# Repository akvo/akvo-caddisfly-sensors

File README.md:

This repository contain source files for fabricating the environmental sensors developed by Akvo in partnership with SODAQ and REGGS. The files are stored in two folders:

*hardware-packaging*: contains design files for the plastic and aluminum components, as well as photography, stickers, and packaging.

The abbreviations stand for:

* WEC: Water EC sensor
* SEC: Soil EC sensor
* SOM: Soil Moisture sensor
* SUM: Stove Usage Monitoring sensor
* WAP: Water pressure sensor
* HAP: House Air Pollution sensor
* SSU: Standard Surface Unit

*pcb-software-manuals*: contains design files for the PCB's, including manuals, firmware and supporting software.

Each device folder includes:

Hardware files : Eagle CAD files for the schematic and gerbers, including a bill of materials (BOM).

Software files : arduino files and associated libraries

Manual : in pdf & markdown format

License
Copyright (C) Stichting Akvo (Akvo Foundation)

The software and the reference designs for the hardware are licensed under CC-BY-SA 3.0

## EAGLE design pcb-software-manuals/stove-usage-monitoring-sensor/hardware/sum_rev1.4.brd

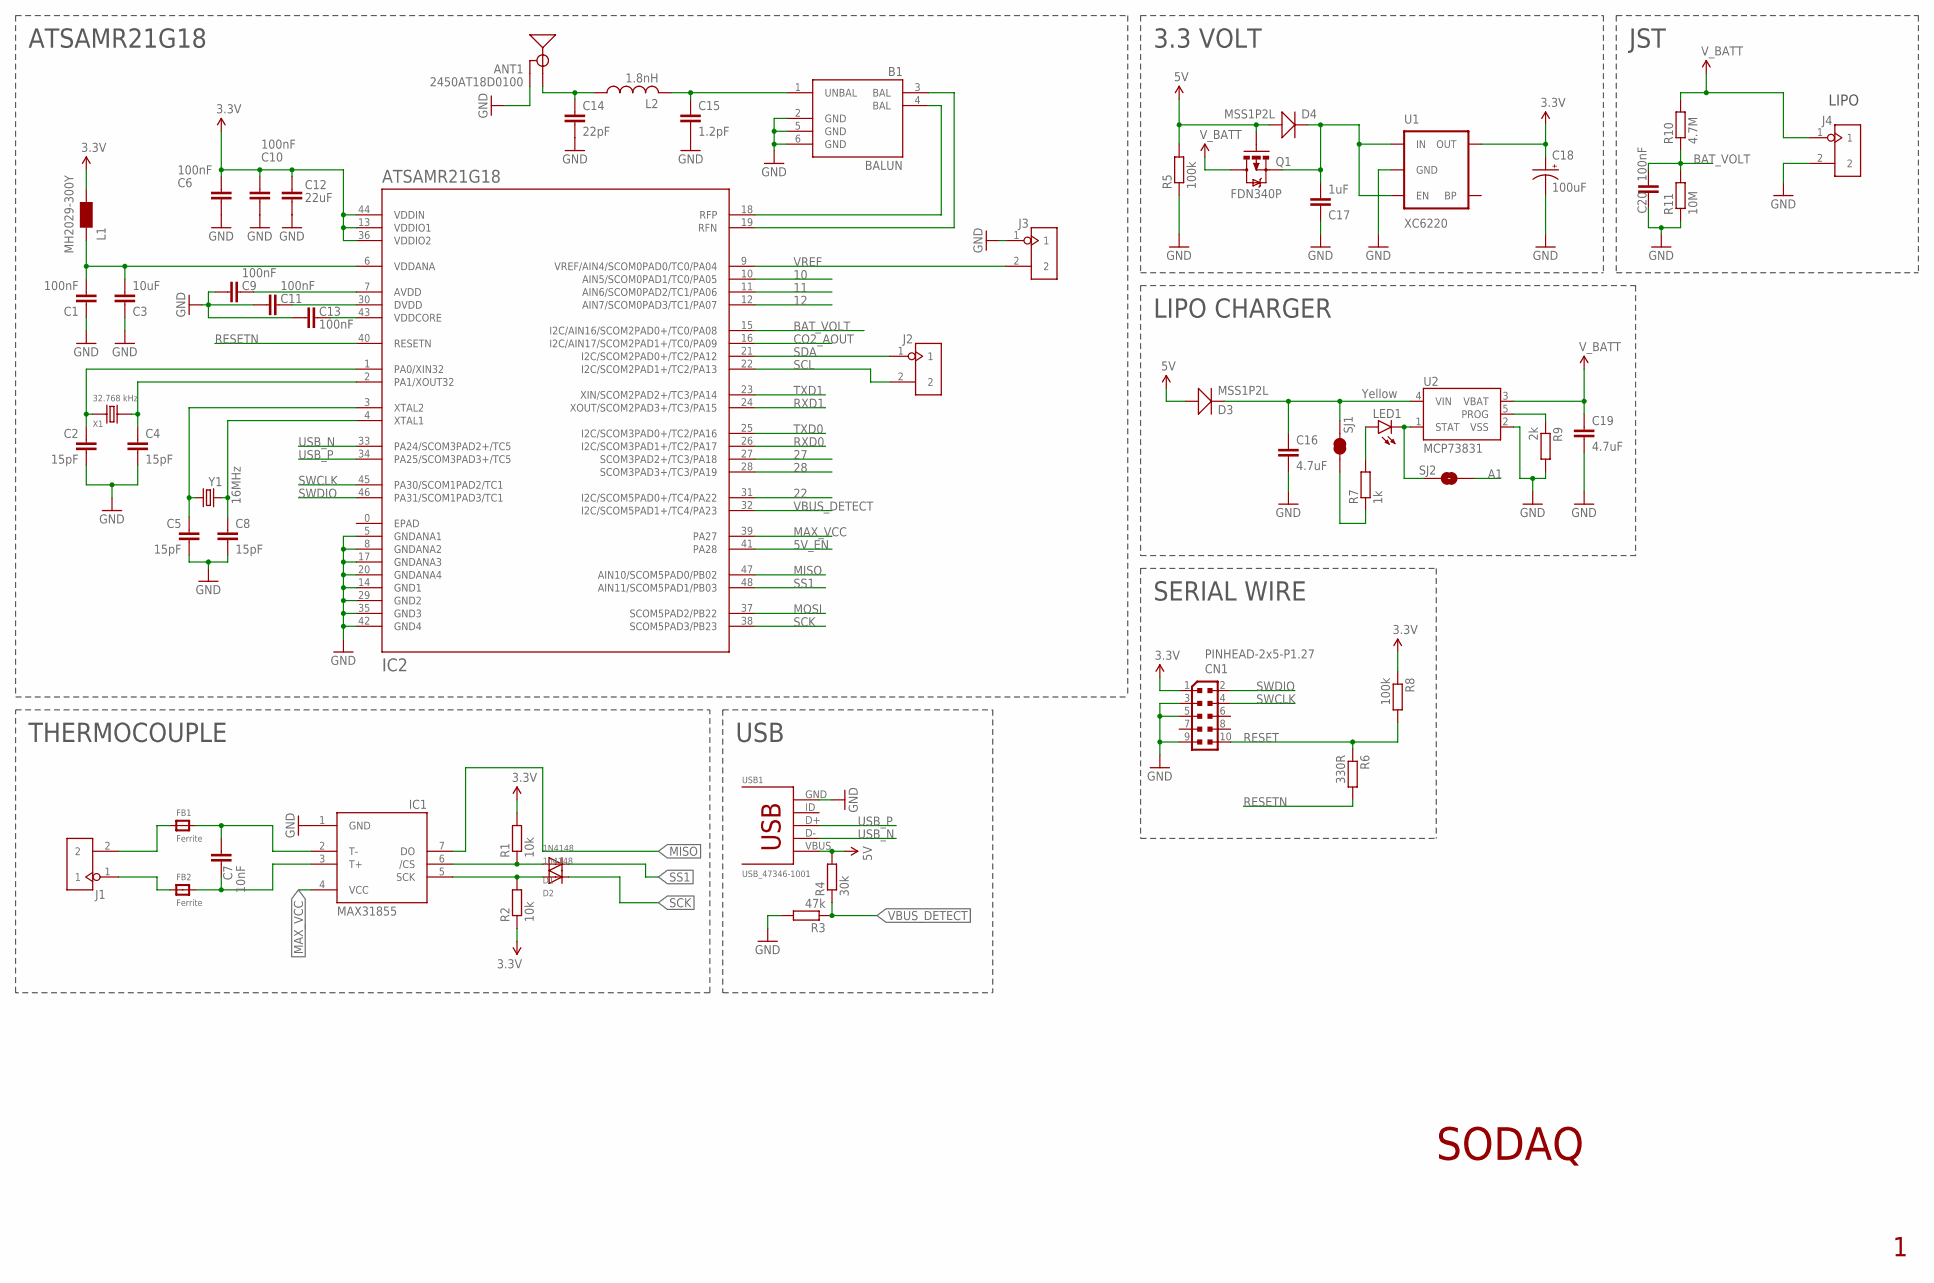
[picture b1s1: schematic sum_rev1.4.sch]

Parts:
ANT1: 2450AT18D0100
B1: BALUN
C1, C6, C9, C10, C11, C13, C20: 100nF; C0402
C2, C4, C5, C8: 15pF; C0402
C3: 10uF; C0402
C7: 10nF; C0402
C12: 22uF; 0805
C14: 22pF; C0402
C15: 1.2pF; C0402
C16, C19: 4.7uF; C0603
C17: 1uF; C0603
C18: 100uF; EIA3216
CN1: PINHEAD-2x5-P1.27; PINHEAD_2X05_127
D1: 1N4148; SOD-323F
D2: 1n4148; SOD-323F
D3, D4: MSS1P2L; D1005
FB1, FB2: Ferrite; _0805
IC1: MAX31855; SO08
IC2: ATSAMR21G18; QFN48_SMALL-CPAD
J1, J2, J3, J4: HEADER-2P-2.0; 2P-2.0
L1: MH2029-300Y; 0805
L2: 1.8nH; L0402
LED1: Yellow; LED-0603
Q1: FDN340P; SOT23-S-PADS
R1, R2: 10k; R0402
R3: 47k; R0402
R4: 30k; R0402
R5, R8: 100k; R0402
R6: 330R; R0402
R7: 1k; R0402
R9: 2k; R0402
R10: 4.7M; R0402
R11: 10M; R0402
SJ1: SOLDERJUMPERNC2; SJ_2S-NOTRACE
SJ2: SOLDERJUMPERNO; SJ_2S-NO
U1: XC6220; SOT23-5
U2: MCP73831; SOT23-5
USB1: USB_47346-1001
X1: 32.768 kHz; 2P-SMD-3.2X1.5
Y1: 16MHz; CRYSTAL-SMD-5X3

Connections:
3.3V: C6.2, C10.2, C12.1, C18.A (+), CN1.1, IC2.13 (VDDIO1), IC2.36 (VDDIO2), IC2.44 (VDDIN), L1.2, R1.2, R2.1, R8.1, U1.5 (OUT)
5V: D3.+, D4.+, Q1.1 (G), R4.2, R5.2, USB1.VBUS
5V_EN: IC2.41 (PA28)
10: IC2.10 (AIN5/SCOM0PAD1/TC0/PA05)
11: IC2.11 (AIN6/SCOM0PAD2/TC1/PA06)
12: IC2.12 (AIN7/SCOM0PAD3/TC1/PA07)
22: IC2.31 (I2C/SCOM5PAD0+/TC4/PA22)
27: IC2.27 (SCOM3PAD2+/TC3/PA18)
28: IC2.28 (SCOM3PAD3+/TC3/PA19)
A1: SJ2.1
BAT_VOLT: C20.2, IC2.15 (I2C/AIN16/SCOM2PAD0+/TC0/PA08), R10.1, R11.2
CO2_AOUT: IC2.16 (I2C/AIN17/SCOM2PAD1+/TC0/PA09)
CS: D1.A, IC1.6 (/CS), R1.1
EPAD: IC2.0 (EPAD)
GND: ANT1.2 (GND), ANT1.3 (GND), ANT1.4 (GND), B1.2 (GND), B1.5 (GND), B1.6 (GND), C1.2, C2.1, C3.2, C4.2, C5.2, C6.1, C8.2, C9.2, C10.1, C11.2, C12.2, C13.2, C14.2, C15.2, C16.2, C17.1, C18.C (-), C19.2, C20.1, CN1.3, CN1.5, CN1.9, IC1.1 (GND), IC2.5 (GNDANA1), IC2.8 (GNDANA2), IC2.14 (GND1), IC2.17 (GNDANA3), IC2.20 (GNDANA4), IC2.29 (GND2), IC2.35 (GND3), IC2.42 (GND4), J3.1, J4.2, R3.2, R5.1, R9.2, R11.1, U1.2 (GND), U2.2 (VSS), USB1.GND
LIPO_STAT: LED1.C, SJ2.2, U2.1 (STAT)
MAX_VCC: IC1.4 (VCC), IC2.39 (PA27)
MISO: IC1.7 (DO), IC2.47 (AIN10/SCOM5PAD0/PB02)
MOSI: IC2.37 (SCOM5PAD2/PB22)
unnamed: ANT1.1 (SIGNAL), C14.1, L2.1
unnamed: FB1.1, J1.2
unnamed: C7.2, FB1.2, IC1.2 (T-)
unnamed: C13.1, IC2.43 (VDDCORE)
unnamed: B1.1 (UNBAL), C15.1, L2.2
unnamed: C11.1, IC2.30 (DVDD)
unnamed: FB2.1, J1.1
unnamed: C9.1, IC2.7 (AVDD)
unnamed: C17.2, D4.-, Q1.2 (S), U1.1 (IN), U1.3 (EN)
unnamed: C2.2, IC2.1 (PA0/XIN32), X1.1
unnamed: LED1.A, R7.2
unnamed: R9.1, U2.5 (PROG)
unnamed: C16.1, D3.-, SJ1.2, U2.4 (VIN)
unnamed: R7.1, SJ1.1
unnamed: C4.1, IC2.2 (PA1/XOUT32), X1.2
unnamed: C1.1, C3.1, IC2.6 (VDDANA), L1.1
unnamed: C5.1, IC2.3 (XTAL2), Y1.1
unnamed: C8.1, IC2.4 (XTAL1), Y1.3 (2)
unnamed: B1.4 (BAL), IC2.18 (RFP)
unnamed: B1.3 (BAL), IC2.19 (RFN)
unnamed: C7.1, FB2.2, IC1.3 (T+)
RESET: CN1.10, R6.1, R8.2
RESETN: IC2.40 (RESETN), R6.2
RXD0: IC2.26 (I2C/SCOM3PAD1+/TC2/PA17)
RXD1: IC2.24 (XOUT/SCOM2PAD3+/TC3/PA15)
SCK: D2.C, IC2.38 (SCOM5PAD3/PB23)
SCK1: D2.A, IC1.5 (SCK), R2.2
SCL: IC2.22 (I2C/SCOM2PAD1+/TC2/PA13), J2.2
SDA: IC2.21 (I2C/SCOM2PAD0+/TC2/PA12), J2.1
SS1: D1.C, IC2.48 (AIN11/SCOM5PAD1/PB03)
SWCLK: CN1.4, IC2.45 (PA30/SCOM1PAD2/TC1)
SWDIO: CN1.2, IC2.46 (PA31/SCOM1PAD3/TC1)
TXD0: IC2.25 (I2C/SCOM3PAD0+/TC2/PA16)
TXD1: IC2.23 (XIN/SCOM2PAD2+/TC3/PA14)
USB_N: IC2.33 (PA24/SCOM3PAD2+/TC5), USB1.D-
USB_P: IC2.34 (PA25/SCOM3PAD3+/TC5), USB1.D+
VBUS_DETECT: IC2.32 (I2C/SCOM5PAD1+/TC4/PA23), R3.1, R4.1
VREF: IC2.9 (VREF/AIN4/SCOM0PAD0/TC0/PA04), J3.2
V_BATT: C19.1, J4.1, Q1.3 (D), R10.2, U2.3 (VBAT)

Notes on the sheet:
SODAQ
USB
SERIAL WIRE
LIPO CHARGER
JST
LIPO
THERMOCOUPLE
ATSAMR21G18
3.3 VOLT

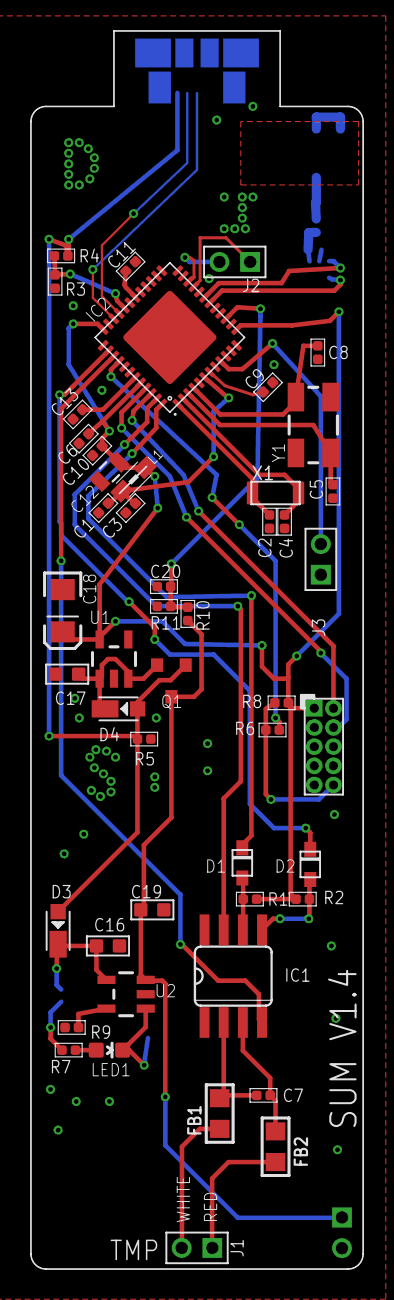
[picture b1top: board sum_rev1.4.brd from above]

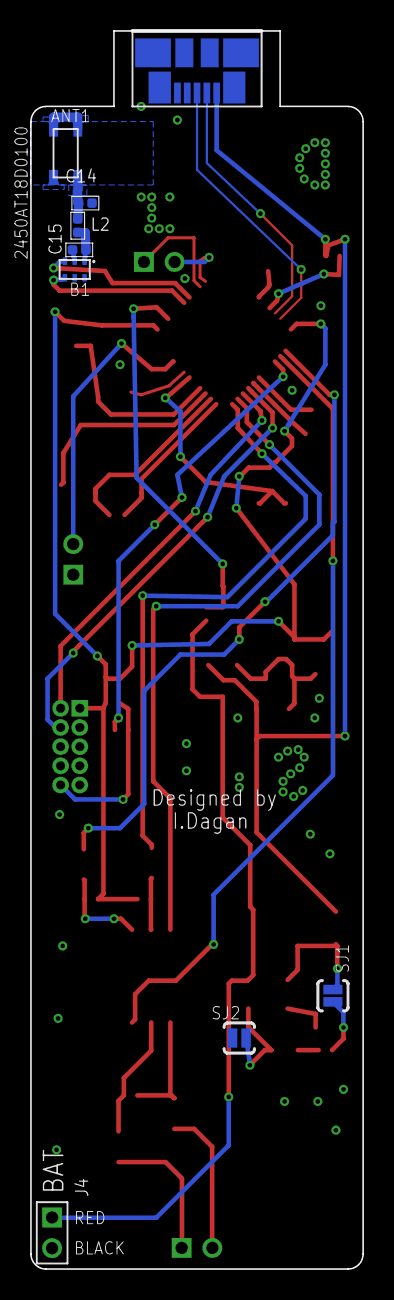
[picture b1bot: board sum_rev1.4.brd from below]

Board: 2 copper layers, 22.0 x 82.0 mm, 57 parts (9 on the bottom side), 43 nets.

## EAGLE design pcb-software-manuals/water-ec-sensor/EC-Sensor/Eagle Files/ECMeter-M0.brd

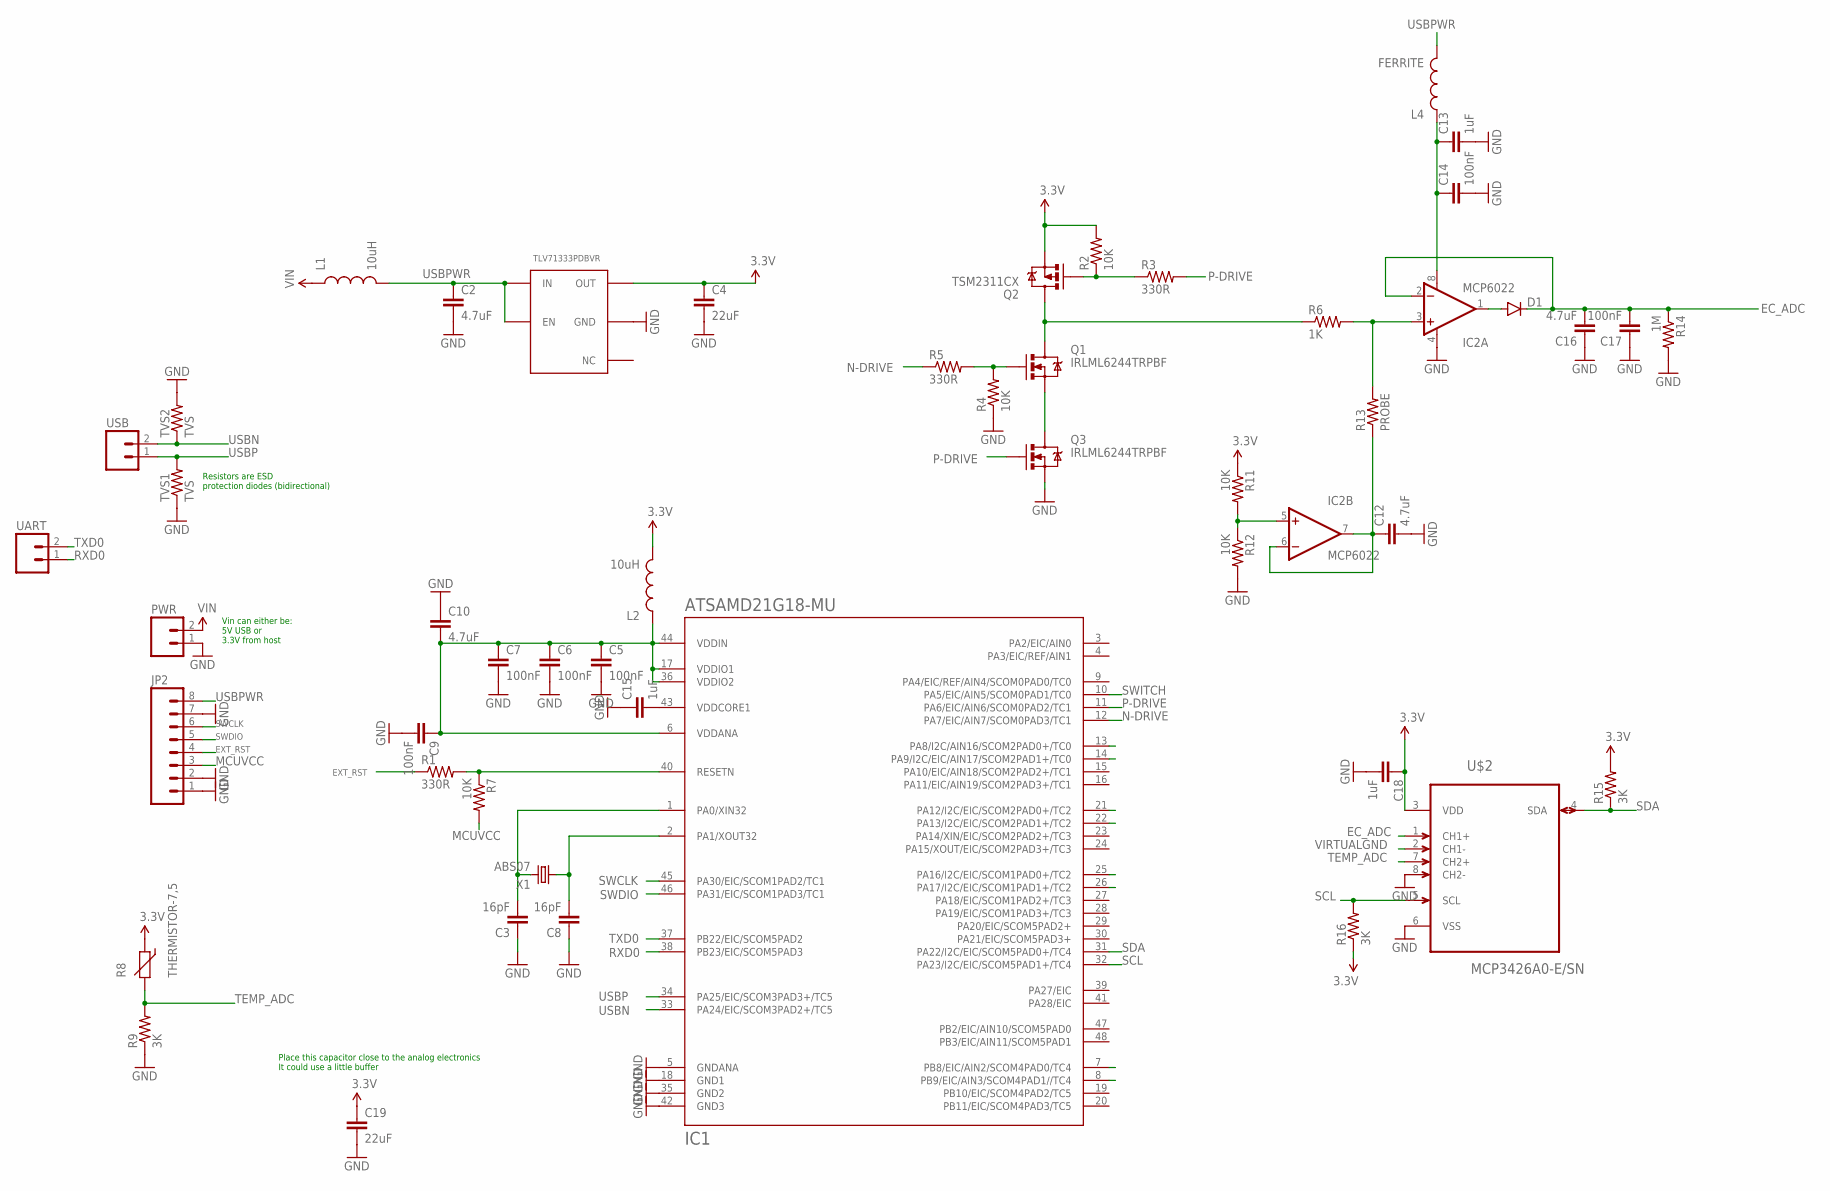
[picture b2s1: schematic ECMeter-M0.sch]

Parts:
C2, C10, C12, C16: 4.7uF; 0805
C3, C8: 16pF; 0402-CAP
C4, C19: 22uF; 0805
C5, C6, C7, C9, C14, C17: 100nF; 0603-CAP
C13, C15, C18: 1uF; 0603-CAP
D1: DIODESOD123; SOD-123
IC1: ATSAMD21G18-MU; QFN48
IC2: MCP6022; SO08
JP2: M08NO_SILK_FEMALE_PTH; 1X08_NO_SILK
L1, L2: 10uH; 0805
L4: FERRITE; 0603
PWR: M02LOCK_LONGPADS; 1X02_LOCK_LONGPADS
Q1, Q3: IRLML6244TRPBF; SOT23-3
Q2: TSM2311CX; SOT23-3
R1, R3, R5: 330R; 0603-RES
R2, R4, R7, R11, R12: 10K; 0603-RES
R6: 1K; 1206
R8: THERMISTOR-7,5; R-7,5
R9, R15, R16: 3K; 0603-RES
R13: PROBE; AXIAL-0.6
R14: 1M; 0603-RES
TVS1, TVS2: TVS; 0603-RES
U$1: TLV71333PDBVR
U$2: MCP3426A0-E/SN; SOIC127P600X175-8N
UART: M02LOCK_LONGPADS; 1X02_LOCK_LONGPADS
USB: M02LOCK_LONGPADS; 1X02_LOCK_LONGPADS
X1: ABS07

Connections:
3.3V: C4.1, C18.1, C19.1, L2.2, Q2.2 (S), R2.2, R8.1, R11.1, R15.2, R16.1, U$1.P$5 (OUT), U$2.3 (VDD)
EC_ADC: C16.2, C17.2, D1.C, IC2.2 (-IN), R14.1, U$2.1 (CH1+)
EXT_RST: JP2.4, R1.1
GND: C2.2, C3.1, C4.2, C5.2, C6.2, C7.2, C8.1, C9.2, C10.1, C12.2, C13.2, C14.2, C15.1, C16.1, C17.1, C18.2, C19.2, IC1.5 (GNDANA), IC1.18 (GND1), IC1.35 (GND2), IC1.42 (GND3), IC2.4 (V-), JP2.1, JP2.2, JP2.7, PWR.1, Q3.2 (S), R4.1, R9.1, R12.2, R14.2, TVS1.1, TVS2.2, U$1.P$2 (GND), U$2.6 (VSS), U$2.8 (CH2-)
MCUVCC: C5.1, C6.1, C7.1, C9.1, C10.2, IC1.6 (VDDANA), IC1.17 (VDDIO1), IC1.36 (VDDIO2), IC1.44 (VDDIN), JP2.3, L2.1, R7.2
unnamed: D1.A, IC2.1 (OUT)
unnamed: IC1.40 (RESETN), R1.2, R7.1
unnamed: C3.2, IC1.1 (PA0/XIN32), X1.P$2 (2)
unnamed: C8.2, IC1.2 (PA1/XOUT32), X1.P$1 (1)
unnamed: Q2.1 (G), R2.1, R3.1
unnamed: Q1.2 (S), Q3.3 (D)
unnamed: Q1.3 (D), Q2.3 (D), R6.1
unnamed: Q1.1 (G), R4.2, R5.2
unnamed: C15.2, IC1.43 (VDDCORE1)
unnamed: IC2.3 (+IN), R6.2, R13.P$2 (2)
unnamed: IC2.5 (+IN), R11.2, R12.1
unnamed: C13.1, C14.1, IC2.8 (V+), L4.1
N-DRIVE: IC1.12 (PA7/EIC/AIN7/SCOM0PAD3/TC1), R5.1
P-DRIVE: IC1.11 (PA6/EIC/AIN6/SCOM0PAD2/TC1), Q3.1 (G), R3.2
RXD0: IC1.38 (PB23/EIC/SCOM5PAD3), UART.1
SCL: IC1.32 (PA23/I2C/EIC/SCOM5PAD1+/TC4), R16.2, U$2.5 (SCL)
SDA: IC1.31 (PA22/I2C/EIC/SCOM5PAD0+/TC4), R15.1, U$2.4 (SDA)
SWCLK: IC1.45 (PA30/EIC/SCOM1PAD2/TC1), JP2.6
SWDIO: IC1.46 (PA31/EIC/SCOM1PAD3/TC1), JP2.5
SWITCH: IC1.10 (PA5/EIC/AIN5/SCOM0PAD1/TC0)
TEMP_ADC: R8.2, R9.2, U$2.7 (CH2+)
TXD0: IC1.37 (PB22/EIC/SCOM5PAD2), UART.2
USBN: IC1.33 (PA24/EIC/SCOM3PAD2+/TC5), TVS2.1, USB.2
USBP: IC1.34 (PA25/EIC/SCOM3PAD3+/TC5), TVS1.2, USB.1
USBPWR: C2.1, JP2.8, L1.2, L4.2, U$1.P$1 (IN), U$1.P$3 (EN)
VIN: L1.1, PWR.2
VIRTUALGND: C12.1, IC2.6 (-IN), IC2.7 (OUT), R13.P$1 (1), U$2.2 (CH1-)

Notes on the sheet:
Resistors are ESD protection diodes (bidirectional)
Vin can either be: 5V USB or 3.3V from host
Place this capacitor close to the analog electronics It could use a little buffer

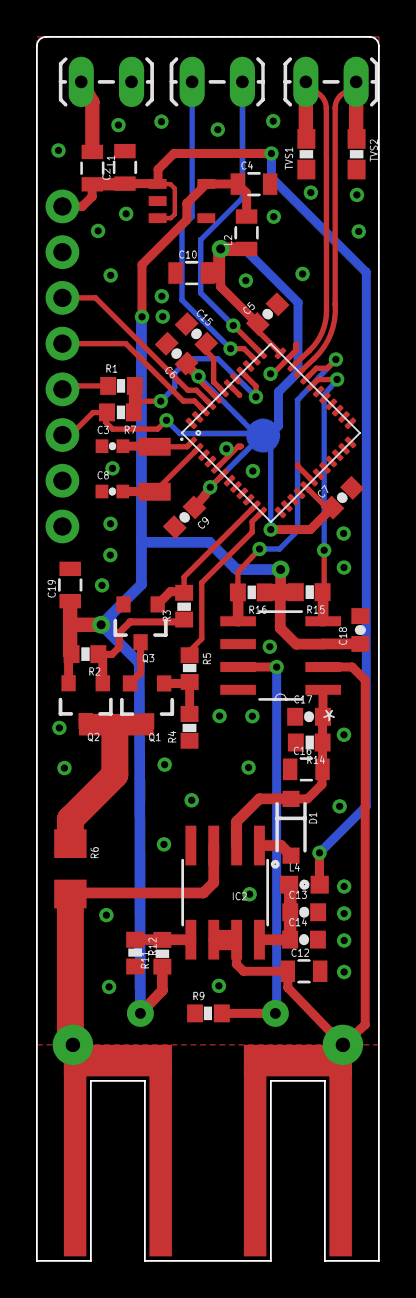
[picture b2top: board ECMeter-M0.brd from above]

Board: 2 copper layers, 19.0 x 68.0 mm, 50 parts (0 on the bottom side), 31 nets.

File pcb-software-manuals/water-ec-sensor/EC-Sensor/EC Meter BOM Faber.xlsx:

Qty | Value | Device | Package | Parts | Description | Farnell #
1 |  | DIODESOD123 | SOD-123 | D1 | Diode | 1829200
6 | 100nF | CAP0603-CAP | 0603 | C5, C6, C7, C9, C14, C17 | Capacitor | 1759122
5 | 10K | RESISTOR0603-RES | 0603 | R2, R4, R7, R11, R12 | Resistor | 2333520
2 | 10uH | INDUCTOR0805 | 0805 | L1, L2 | Inductors | 2215650
2 | 16pF | CAP0402-CAP | 0402 | C3, C8 | Capacitor | 2218841
1 | 1K | RESISTOR1206 | 1206 | R6 | Resistor | 2447473
1 | 1M | RESISTOR0603-RES | 0603 | R14 | Resistor | 2321755
3 | 1uF | CAP0603-CAP | 0603 | C13, C15, C18 | Capacitor | 1759408
2 | 22uF | CAP0805 | 0805 | C4, C19 | Capacitor | 1108326
3 | 330R | RESISTOR0603-RES | 0603 | R1, R3, R5 | Resistor | 9238425
3 | 3K | RESISTOR0603-RES | 0603 | R9, R15, R16 | Resistor | 9330976
4 | 4.7uF | CAP0805 | 0805 | C2, C10, C12, C16 | Capacitor | 2118133
1 | ABS07 | ABS07 | ABS07 | X1 |  | 2467864
1 | ATSAMD21G18-MU | ATSAMD21G18-MU | QFN48 | IC1 |  | 2409249
1 | FERRITE | INDUCTOR0603 | 0603 | L4 | Inductors | 1515671
2 | IRLML6244TRPBF | MOSFET-NCHANNELAO3404A | SOT23-3 | Q1, Q3 | Common NMOSFET Parts | 1864517
1 | MCP3426A0-E/SN | MCP3426A0-E/SN | SOIC127P600X175-8N | U$2 | Analog-to-Digital Converter | 1825012
1 | MCP6022 | OPAMP-DUALU | SO08 | IC2 | Generic op-amp footprint | 1332126
1 | THERMISTOR-7,5 | THERMISTOR-7,5 | Through-hole | R8 | THERMISTOR | 1888078
1 | TLV71333PDBVR | TLV71333PDBVR | TLV71333PDBVR | U$1 |  | 2463932
1 | TSM2311CX | MOSFET-PCHANNEL | SOT23-3 | Q2 | Generic PMOSFET | 1864586
2 | TVS | RESISTOR0603-RES | 0603-RES | TVS1, TVS2 | Resistor | 2368173

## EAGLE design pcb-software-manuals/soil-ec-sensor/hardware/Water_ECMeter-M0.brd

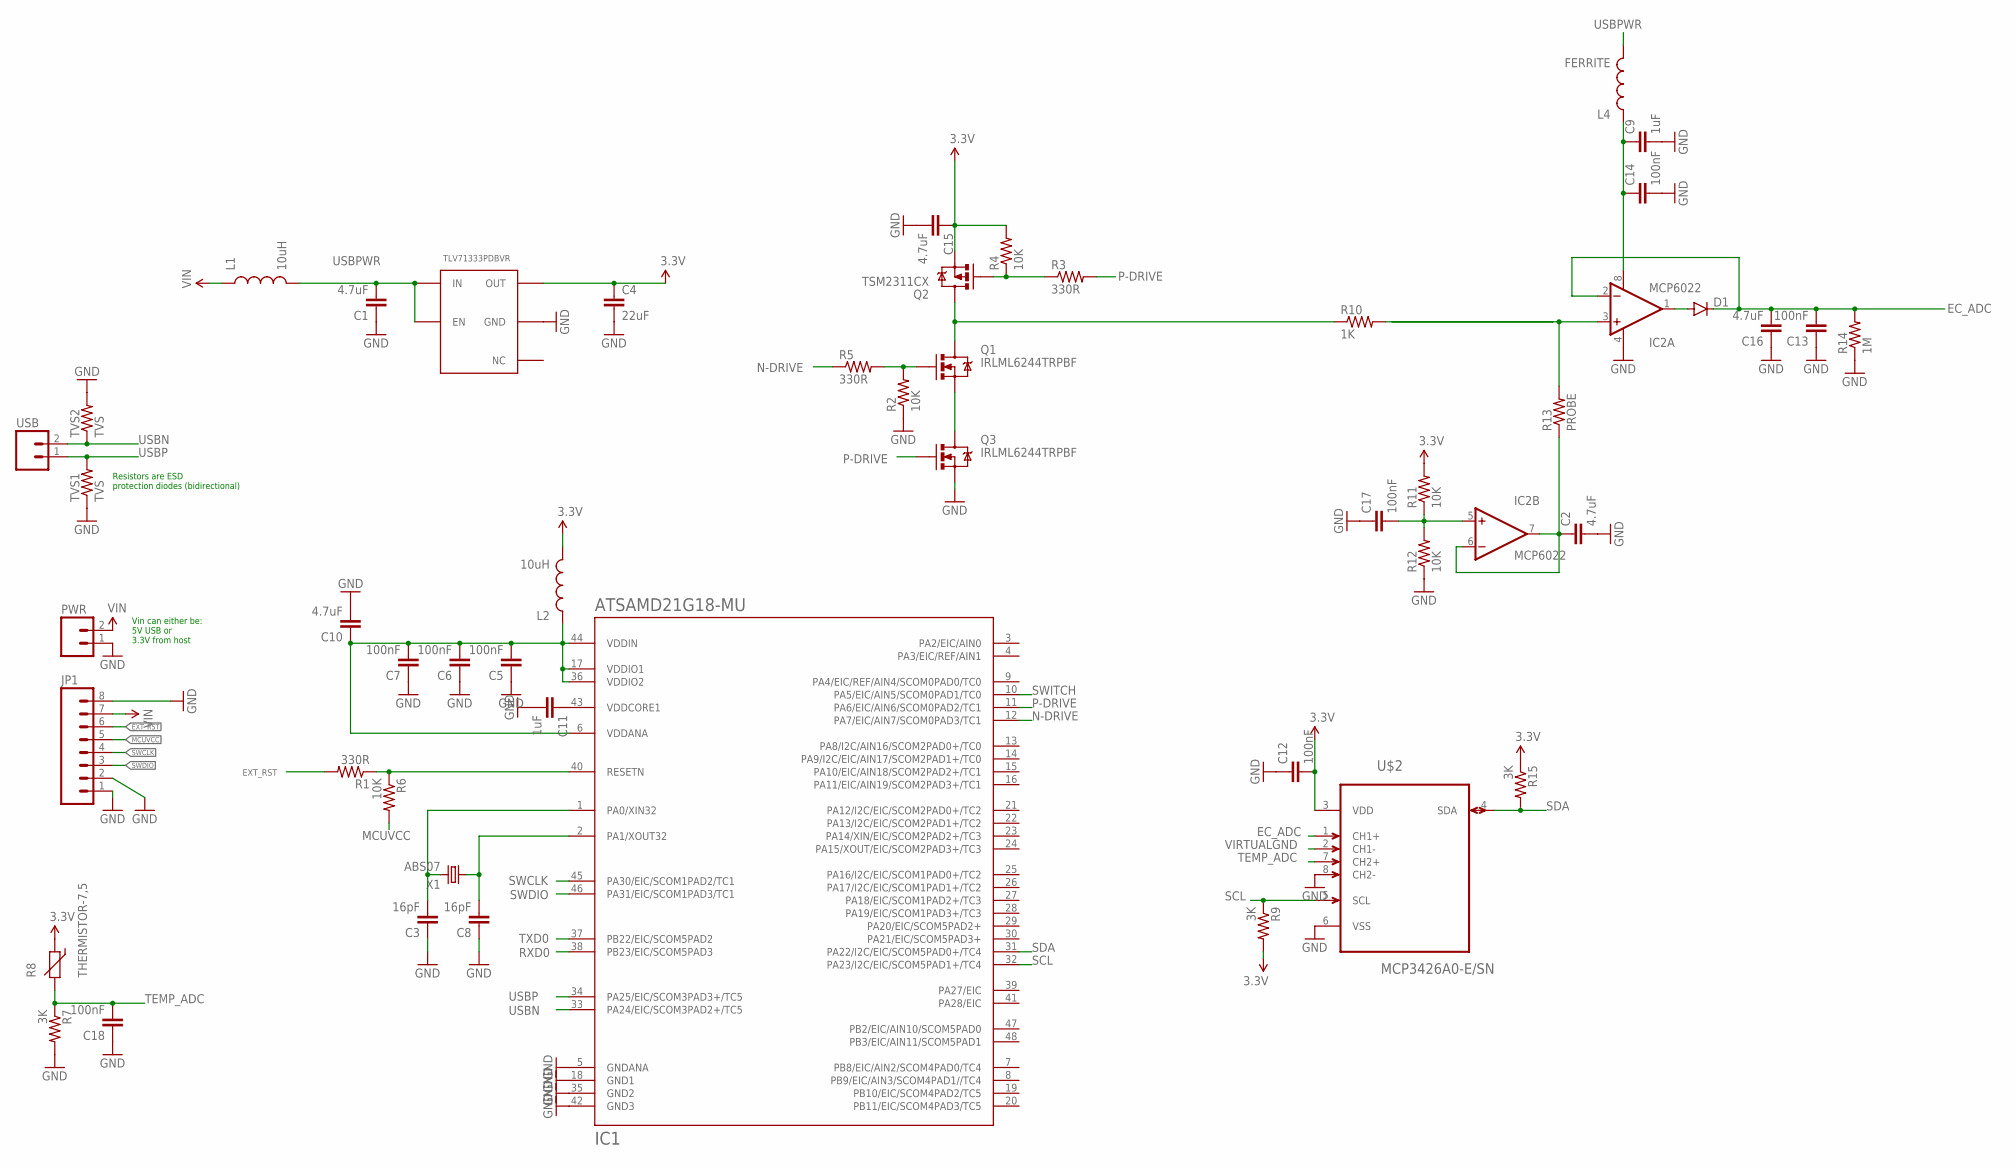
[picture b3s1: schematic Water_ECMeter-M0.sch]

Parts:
C1, C2, C10, C15, C16: 4.7uF; 0603-CAP
C3, C8: 16pF; 0402-CAP
C4: 22uF; 1206
C5, C6, C7, C12, C13, C14, C17, C18: 100nF; 0402-CAP
C9, C11: 1uF; 0402-CAP
D1: DIODESOD123; SOD-123
IC1: ATSAMD21G18-MU; QFN48
IC2: MCP6022; SO08
JP1: M08; 1X08_ROUND
L1, L2: 10uH; 0603
L4: FERRITE; 0603
PWR: M02LOCK_LONGPADS; 1X02_LOCK_LONGPADS
Q1, Q3: IRLML6244TRPBF; SOT23-3
Q2: TSM2311CX; SOT23-3
R1, R3, R5: 330R; 0402-RES
R2, R4, R6, R11, R12: 10K; 0402-RES
R7, R9, R15: 3K; 0402-RES
R8: THERMISTOR-7,5; R-7,5
R10: 1K; 0805
R13: PROBE; AXIAL-0.6
R14: 1M; 0402-RES
TVS1, TVS2: TVS; 0402-RES
U$1: TLV71333PDBVR
U$2: MCP3426A0-E/SN; SOIC127P600X175-8N
USB: M02LOCK_LONGPADS; 1X02_LOCK_LONGPADS
X1: ABS07

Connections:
3.3V: C4.1, C12.2, C15.1, L2.2, Q2.2 (S), R4.2, R8.1, R9.2, R11.2, R15.1, U$1.P$5 (OUT), U$2.3 (VDD)
EC_ADC: C13.2, C16.2, D1.C, IC2.2 (-IN), R14.2, U$2.1 (CH1+)
EXT_RST: JP1.6, R1.2
GND: C1.1, C2.2, C3.1, C4.2, C5.1, C6.1, C7.1, C8.1, C9.2, C10.2, C11.2, C12.1, C13.1, C14.2, C15.2, C16.1, C17.1, C18.1, IC1.5 (GNDANA), IC1.18 (GND1), IC1.35 (GND2), IC1.42 (GND3), IC2.4 (V-), JP1.1, JP1.2, JP1.8, PWR.1, Q3.2 (S), R2.1, R7.2, R12.1, R14.1, TVS1.1, TVS2.2, U$1.P$2 (GND), U$2.6 (VSS), U$2.8 (CH2-)
MCUVCC: C5.2, C6.2, C7.2, C10.1, IC1.6 (VDDANA), IC1.17 (VDDIO1), IC1.36 (VDDIO2), IC1.44 (VDDIN), JP1.5, L2.1, R6.2
unnamed: D1.A, IC2.1 (OUT)
unnamed: IC1.40 (RESETN), R1.1, R6.1
unnamed: C3.2, IC1.1 (PA0/XIN32), X1.P$2 (2)
unnamed: C11.1, IC1.43 (VDDCORE1)
unnamed: C8.2, IC1.2 (PA1/XOUT32), X1.P$1 (1)
unnamed: Q2.1 (G), R3.1, R4.1
unnamed: Q1.2 (S), Q3.3 (D)
unnamed: Q1.3 (D), Q2.3 (D), R10.1
unnamed: Q1.1 (G), R2.2, R5.2
unnamed: IC2.3 (+IN), R10.2, R13.P$2 (2)
unnamed: C17.2, IC2.5 (+IN), R11.1, R12.2
unnamed: C9.1, C14.1, IC2.8 (V+), L4.1
N-DRIVE: IC1.12 (PA7/EIC/AIN7/SCOM0PAD3/TC1), R5.1
P-DRIVE: IC1.11 (PA6/EIC/AIN6/SCOM0PAD2/TC1), Q3.1 (G), R3.2
RXD0: IC1.38 (PB23/EIC/SCOM5PAD3)
SCL: IC1.32 (PA23/I2C/EIC/SCOM5PAD1+/TC4), R9.1, U$2.5 (SCL)
SDA: IC1.31 (PA22/I2C/EIC/SCOM5PAD0+/TC4), R15.2, U$2.4 (SDA)
SWCLK: IC1.45 (PA30/EIC/SCOM1PAD2/TC1), JP1.4
SWDIO: IC1.46 (PA31/EIC/SCOM1PAD3/TC1), JP1.3
SWITCH: IC1.10 (PA5/EIC/AIN5/SCOM0PAD1/TC0)
TEMP_ADC: C18.2, R7.1, R8.2, U$2.7 (CH2+)
TXD0: IC1.37 (PB22/EIC/SCOM5PAD2)
USBN: IC1.33 (PA24/EIC/SCOM3PAD2+/TC5), TVS2.1, USB.2
USBP: IC1.34 (PA25/EIC/SCOM3PAD3+/TC5), TVS1.2, USB.1
USBPWR: C1.2, L1.2, L4.2, U$1.P$1 (IN), U$1.P$3 (EN)
VIN: JP1.7, L1.1, PWR.2
VIRTUALGND: C2.1, IC2.6 (-IN), IC2.7 (OUT), R13.P$1 (1), U$2.2 (CH1-)

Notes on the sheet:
Resistors are ESD protection diodes (bidirectional)
Vin can either be: 5V USB or 3.3V from host

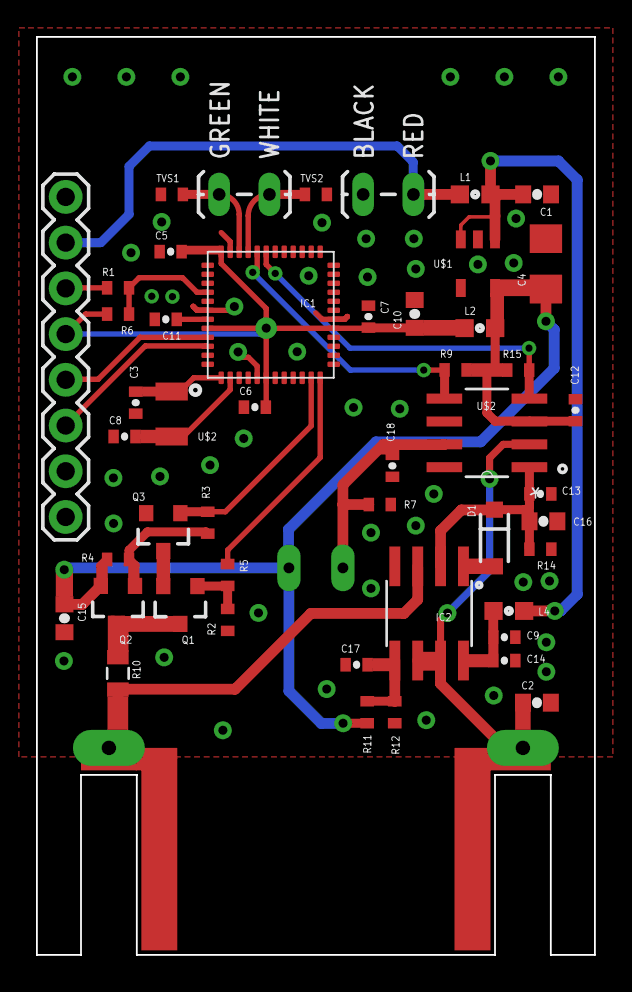
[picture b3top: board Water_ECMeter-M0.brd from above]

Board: 2 copper layers, 31.0 x 51.0 mm, 50 parts (0 on the bottom side), 29 nets.

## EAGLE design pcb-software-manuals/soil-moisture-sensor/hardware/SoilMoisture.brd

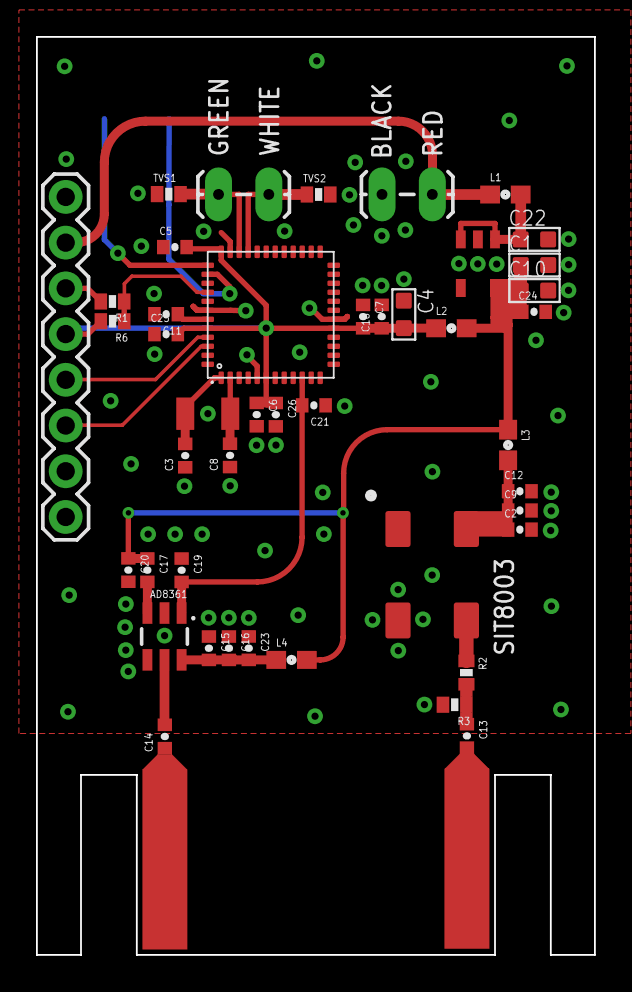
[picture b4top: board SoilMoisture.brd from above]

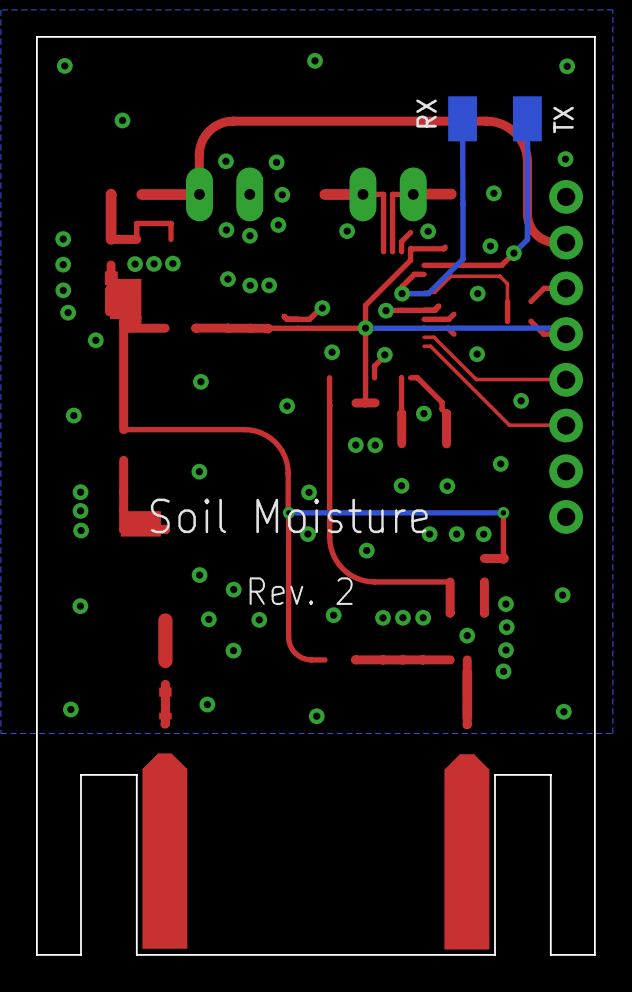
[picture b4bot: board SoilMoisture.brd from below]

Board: 2 copper layers, 31.0 x 51.0 mm, 46 parts (2 on the bottom side), 23 nets.

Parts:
AD8361: AD8361; SOT23-6
C1, C4, C10, C22: 10uF; C0603
C2, C13, C14, C15, C18, C21, C24, C26: 680pF; 0402-CAP
C3, C8: 12.5pF; 0402-CAP
C5, C6, C7, C9, C16, C17, C19, C20, C25: 100nF; 0402-CAP
C11, C12, C23: 1uF; 0402-CAP
JP1: 1X08_ROUND
L1, L2, L3, L4: 470nH; 0603
MCU: ATSAMD21G18-MU; QFN48
PWR: 1X02_LOCK_LONGPADS
R1: 330R; 0402-RES
R2, R3: 1K; 0402-RES
R6: 10K; 0402-RES
REGULATOR: TLV71333PDBVR
RX: TPSQTP20SQ; TP20SQ
SIT8003: SIT8003
TVS1, TVS2: TVS; 0402-RES
TX: TPSQTP20SQ; TP20SQ
USB: 1X02_LOCK_LONGPADS
X1: ABS07

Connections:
3.3V: C1.1, C10.1, C17.1, C20.1, C24.1, L2.2, L3.1, L4.2, REGULATOR.P$5
EXT_RST: JP1.6, R1.2
GND: AD8361.2, AD8361.4, C1.2, C2.2, C3.1, C4.1, C5.1, C6.2, C7.1, C8.1, C9.2, C10.2, C11.2, C12.2, C15.1, C16.1, C18.2, C19.1, C20.2, C21.1, C22.2, C23.1, C24.2, C25.1, C26.2, JP1.1, JP1.2, JP1.8, MCU.5, MCU.18, MCU.35, MCU.42, PWR.1, R3.2, REGULATOR.P$2, SIT8003.P$2, TVS1.1, TVS2.2
MCUVCC: C4.2, C5.2, C6.1, C7.2, C18.1, C25.2, C26.1, JP1.5, L2.1, MCU.6, MCU.17, MCU.36, MCU.44, R6.2
unnamed: C2.1, C9.1, C12.1, L3.2, SIT8003.P$4
unnamed: MCU.40, R1.1, R6.1
unnamed: C3.2, MCU.1, X1.P$2
unnamed: C11.1, MCU.43
unnamed: C8.2, MCU.2, X1.P$1
unnamed: R2.1, SIT8003.P$3
unnamed: C13.1, R2.2, R3.1
unnamed: AD8361.5, C14.2
unnamed: AD8361.3, C17.2
unnamed: AD8361.6, C15.2, C16.2, C23.2, L4.1
RMS_OUT: AD8361.1, C19.2, C21.2, MCU.10
RXD0: MCU.38, RX.TP
SWCLK: JP1.4, MCU.45
SWDIO: JP1.3, MCU.46
TXD0: MCU.37, TX.TP
USBN: MCU.33, TVS2.1, USB.2
USBP: MCU.34, TVS1.2, USB.1
USBPWR: C22.1, L1.2, REGULATOR.P$1, REGULATOR.P$3
VIN: JP1.7, L1.1, PWR.2

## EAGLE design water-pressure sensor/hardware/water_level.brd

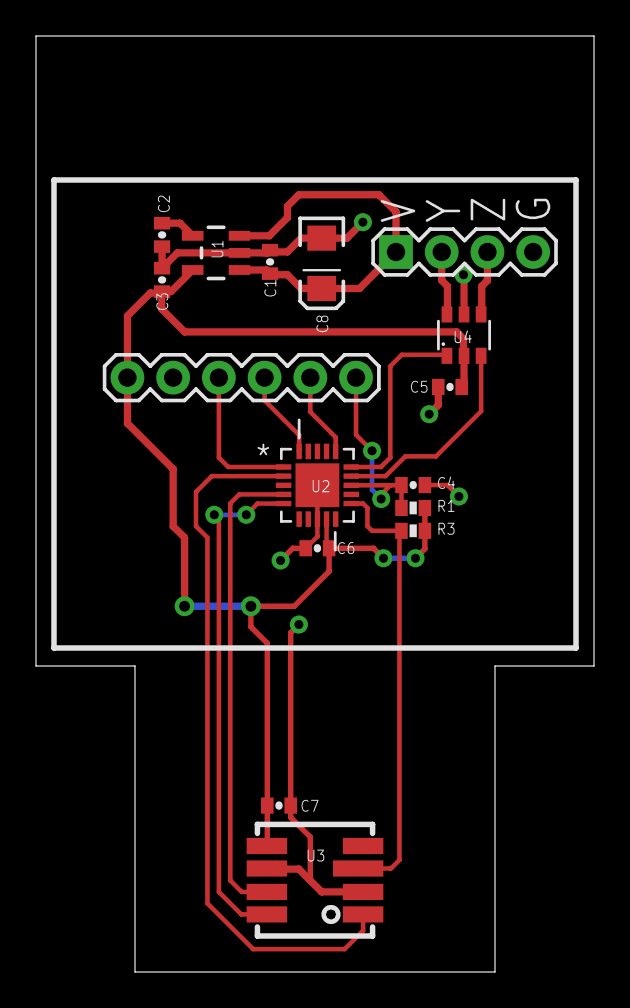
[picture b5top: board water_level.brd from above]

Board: 2 copper layers, 31.0 x 52.0 mm, 16 parts (0 on the bottom side), 16 nets.

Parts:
C1, C3: 2.2uF; 0402-CAP
C2: 10nF; 0402-CAP
C4, C5, C6, C7: 100nF; 0402-CAP
C8: 10uF/16v; EIA3216
JP1: 1X06
JP2: 1X04
R1, R3: 10K; 0402-RES
U1: LP3985; SOT23-5
U2: ATTINY441-MU; QFN50P400X400X80-21N
U3: MS5803-14BA; MS5803
U4: ISL32614E; SOT23-6

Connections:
3.3V: C3.1, C5.1, C6.1, C7.1, JP1.6, R1.2, R3.2, U1.5, U2.9, U3.5, U4.2
CS: R3.1, U2.11, U3.3
DE: U2.14, U4.3
GND: C1.2, C2.2, C3.2, C4.2, C5.2, C6.2, C7.2, C8.C, JP1.5, JP2.4, U1.2, U2.8, U2.GND_PAD, U3.2, U3.6, U4.5
MISO: U2.5, U3.8
MISO_ISP: JP1.3, U2.20
MOSI: U2.4, U3.7
MOSI_ISP: JP1.2, U2.16
unnamed: C2.1, U1.4
RESET: C4.1, JP1.1, R1.1, U2.13
SCK: U2.2, U3.1
SCK_ISP: JP1.4, U2.1
TX: U2.15, U4.1
VIN: C1.1, C8.A, JP2.1, U1.1, U1.3
Y: JP2.2, U4.6
Z: JP2.3, U4.4

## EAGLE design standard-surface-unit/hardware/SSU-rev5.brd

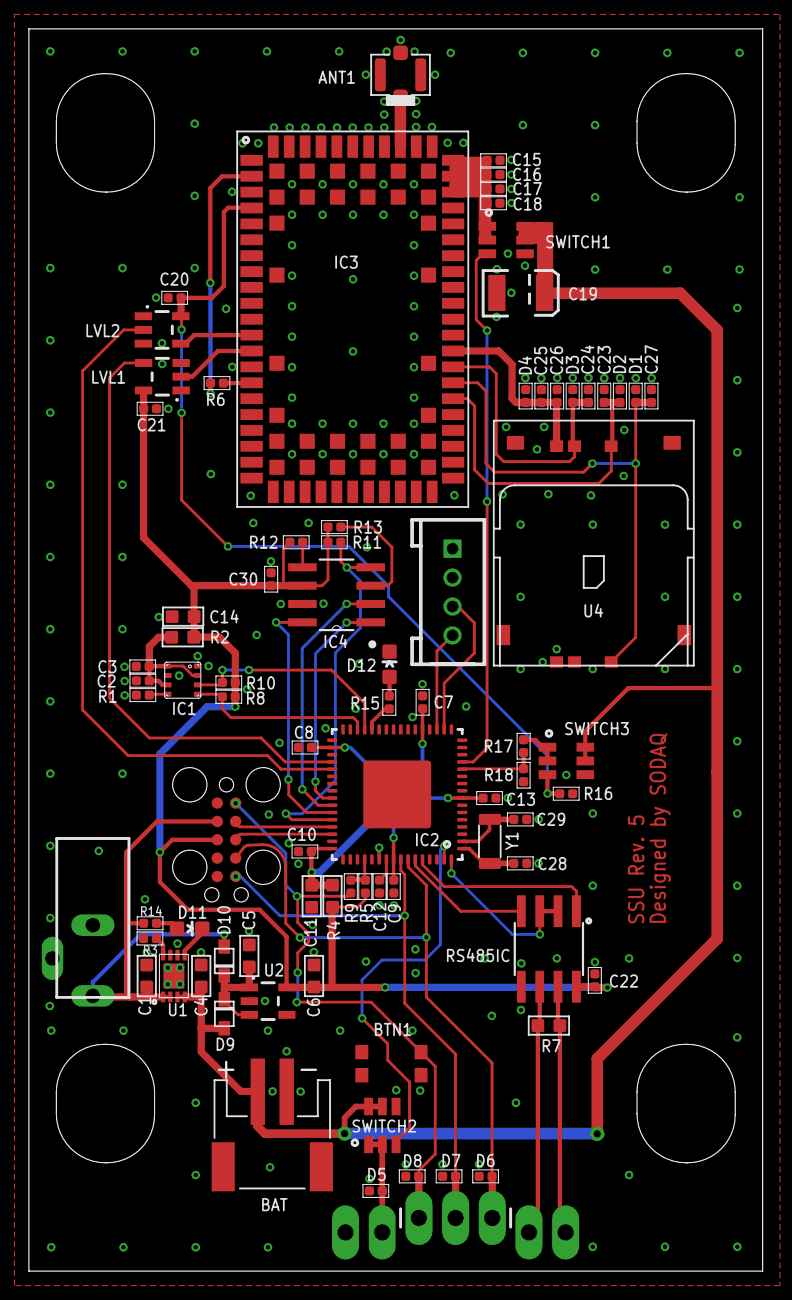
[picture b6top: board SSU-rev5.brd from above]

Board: 2 copper layers, 50.8 x 86.0 mm, 83 parts (0 on the bottom side), 55 nets.

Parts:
ANT1: UFL; U-FL
BAT: JST-PH-2-SMT-RA
BTN1: KMR2BUTTON
C1, C4, C5, C6, C11, C14: 10uF; C0603
C2, C3, C7, C8, C9, C10, C13, C18, C20, C21, C22, C26, C30: 100nF; C0402
C12: 1uF; C0402
C15, C28, C29: 15pF; C0402
C16, C23, C24, C25, C27: 56pF; C0402
C17: 10nF; C0402
C19: 220uF; EIA3528
CONN1: TC-10PIN; TC2050-IDC
D1, D2, D3, D4, D5, D6, D7, D8: ESD_DIODE; R0402
D9, D10: SOD-323F
D11, D12: Yellow; LED-0603
IC1: BME280
IC2: ATSAMD21J18-MU; QFN64
IC3: UBLOX_SARA_U2STANDARD; SARA-U2
IC4: AT45DB161E; SOIC127P600X175-8N
J1: 4P-2.0; HW4-2.0
JACK1: SSU-POWER-JACK
LVL1, LVL2: SN74LV1T34DBVR; SOT23-5
PWR: 1X02_LONGPADS
R1: 0R; R0402
R2, R4: FERRITE; R0603
R3: 2K; R0402
R5, R16, R18: 10K; R0402
R6, R11, R12, R13: 100K; R0402
R7: 120R; R0603
R8, R10, R17: 3K; R0402
R9, R14, R15: 300R; R0402
RS485: 1X02_LONGPADS
RS485IC: SP3485; SO08
SWD: 1X03_LONGPADS
SWITCH1, SWITCH2, SWITCH3: SIP32510; TSOT23-6
U1: MCP73831; DFN8-2X3MM
U2: XC6220; SOT23-5
U4: MICRO_SIM_6P_MOLEX; MICRO_SIM_78800-0001
Y1: 32.768KHZ; X2-SMD-3.2X1.5X0.55MM

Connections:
1.8V: C20.1, IC3.4, LVL2.5, R16.2, SWITCH3.P$3
2G_ENABLE: IC2.13, SWITCH1.P$3
3.3V: C6.1, C14.1, C21.1, C22.2, C30.1, CONN1.3, IC4.6, LVL1.5, R2.2, R4.2, R5.2, R8.1, R10.1, R11.2, R12.2, R13.2, RS485IC.8, U2.5
A: R7.1, RS485.1, RS485IC.6
B: R7.2, RS485.2, RS485IC.7
FLASH_CS: IC2.44, IC4.4, R11.1
FLASH_RESET: IC4.3, R13.1
GND: ANT1.GND1, ANT1.GND2, ANT1.GND3, BAT.2, BTN1.B1, BTN1.B2, C1.2, C2.2, C3.2, C4.2, C5.2, C6.2, C7.2, C8.2, C9.2, C10.2, C11.2, C12.1, C13.2, C14.2, C15.2, C16.2, C17.2, C18.2, C19.C, C20.2, C21.2, C22.1, C23.2, C24.2, C25.2, C26.2, C27.2, C28.1, C29.1, C30.2, CONN1.1, D1.2, D2.2, D3.2, D4.2, D5.2, D6.2, D7.2, D8.2, D12.C, IC1.1, IC1.7, IC2.7, IC2.22, IC2.33, IC2.47, IC2.54, IC3.1, IC3.3, IC3.5, IC3.10, IC3.14, IC3.20, IC3.21, IC3.22, IC3.30, IC3.32, IC3.43, IC3.50, IC3.54, IC3.55, IC3.57, IC3.58, IC3.59, IC3.60, IC3.61, IC3.63, IC3.64, IC3.65, IC3.66, IC3.67, IC3.68, IC3.69, IC3.70, IC3.71, IC3.72, IC3.73, IC3.74, IC3.75, IC3.76, IC3.77, IC3.78, IC3.79, IC3.80, IC3.81, IC3.82, IC3.83, IC3.84, IC3.85, IC3.86, IC3.87, IC3.88, IC3.89, IC3.90, IC3.91, IC3.92, IC3.93, IC3.94, IC3.95, IC3.96, IC4.7, J1.1, JACK1.P$2, LVL1.3, LVL2.3, PWR.1, R1.2, R3.1, R16.1, R18.1, RS485IC.5, SWITCH1.P$4, SWITCH2.P$4, SWITCH3.P$4, U1.6, U1.C_PAD, U2.2, U4.C5
MCU_RESET: BTN1.A2, CONN1.10, D8.1, R9.2, SWD.1
MISO: IC2.43, IC4.8
MOSI: IC2.41, IC4.1
unnamed: C12.2, IC2.55
unnamed: IC2.52, R5.1, R9.1
unnamed: C28.2, IC2.1, Y1.2
unnamed: IC1.5, R1.1
unnamed: C7.1, C8.1, C9.1, C10.1, C11.1, C13.1, IC2.8, IC2.21, IC2.34, IC2.48, IC2.56, R4.1
unnamed: R3.2, U1.8
unnamed: C29.2, IC2.2, Y1.1
unnamed: IC2.18, J1.3
unnamed: ANT1.D, IC3.56
unnamed: IC3.2, R6.2
unnamed: IC3.15, R6.1
unnamed: C2.1, C3.1, IC1.2, IC1.6, IC1.8, R2.1
unnamed: C15.1, C16.1, C17.1, C18.1, IC3.51, IC3.52, IC3.53, SWITCH1.P$1, SWITCH1.P$2
unnamed: IC2.19, J1.4
unnamed: D5.1, PWR.2, SWITCH2.P$1, SWITCH2.P$2
unnamed: C5.1, D9.C, D10.C, U2.1, U2.3
unnamed: D11.C, U1.5
unnamed: D11.A, R14.1
unnamed: IC2.28, R15.2
unnamed: D12.A, R15.1
unnamed: R17.2, SWITCH3.P$1, SWITCH3.P$2
RS485_DATA_IN: IC2.59, RS485IC.4
RS485_DATA_OUT: IC2.60, RS485IC.1
RS485_DIRECTION: IC2.64, RS485IC.2, RS485IC.3
SARA_RX_1.8: IC3.12, LVL2.4
SARA_RX_3.3: IC2.37, LVL2.2
SARA_TX_1.8: IC3.13, LVL1.2
SARA_TX_3.3: IC2.36, LVL1.4
SCL: IC1.4, IC2.30, R8.2
SDA: IC1.3, IC2.29, R10.2
SIM_CLK: C23.1, D2.1, IC3.38, U4.C3
SIM_IO: C27.1, D1.1, IC3.39, U4.C7
SIM_RST: C24.1, D3.1, IC3.40, U4.C2
SIM_VCC: C25.1, C26.1, D4.1, IC3.41, U4.C1
SPICLK: IC2.42, IC4.2
SWCLK: CONN1.6, D7.1, IC2.57, SWD.2
SWDIO: CONN1.7, D6.1, IC2.58, SWD.3
UBLOX_SENSE: IC2.12, R17.1, R18.2
USBN: CONN1.9, IC2.45
USBP: CONN1.8, IC2.46
VIN: C1.1, CONN1.2, D10.A, JACK1.P$1, R14.2, U1.1, U1.2
V_BATT: BAT.1, C4.1, C19.A, D9.A, SWITCH1.P$5, SWITCH1.P$6, SWITCH2.P$5, SWITCH2.P$6, SWITCH3.P$5, SWITCH3.P$6, U1.3, U1.4
WAP_ENABLE: IC2.63, SWITCH2.P$3
WP: IC4.5, R12.1

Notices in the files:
parts and their libraries:
SparkFun-Capacitors: Licensing: CC v3.0 Share-Alike You are welcome to use this library for commercial purposes.
SparkFun-Connectors: Licensing: Creative Commons ShareAlike 4.0 International - https://creativecommons.org/licenses/by-sa/4.0
